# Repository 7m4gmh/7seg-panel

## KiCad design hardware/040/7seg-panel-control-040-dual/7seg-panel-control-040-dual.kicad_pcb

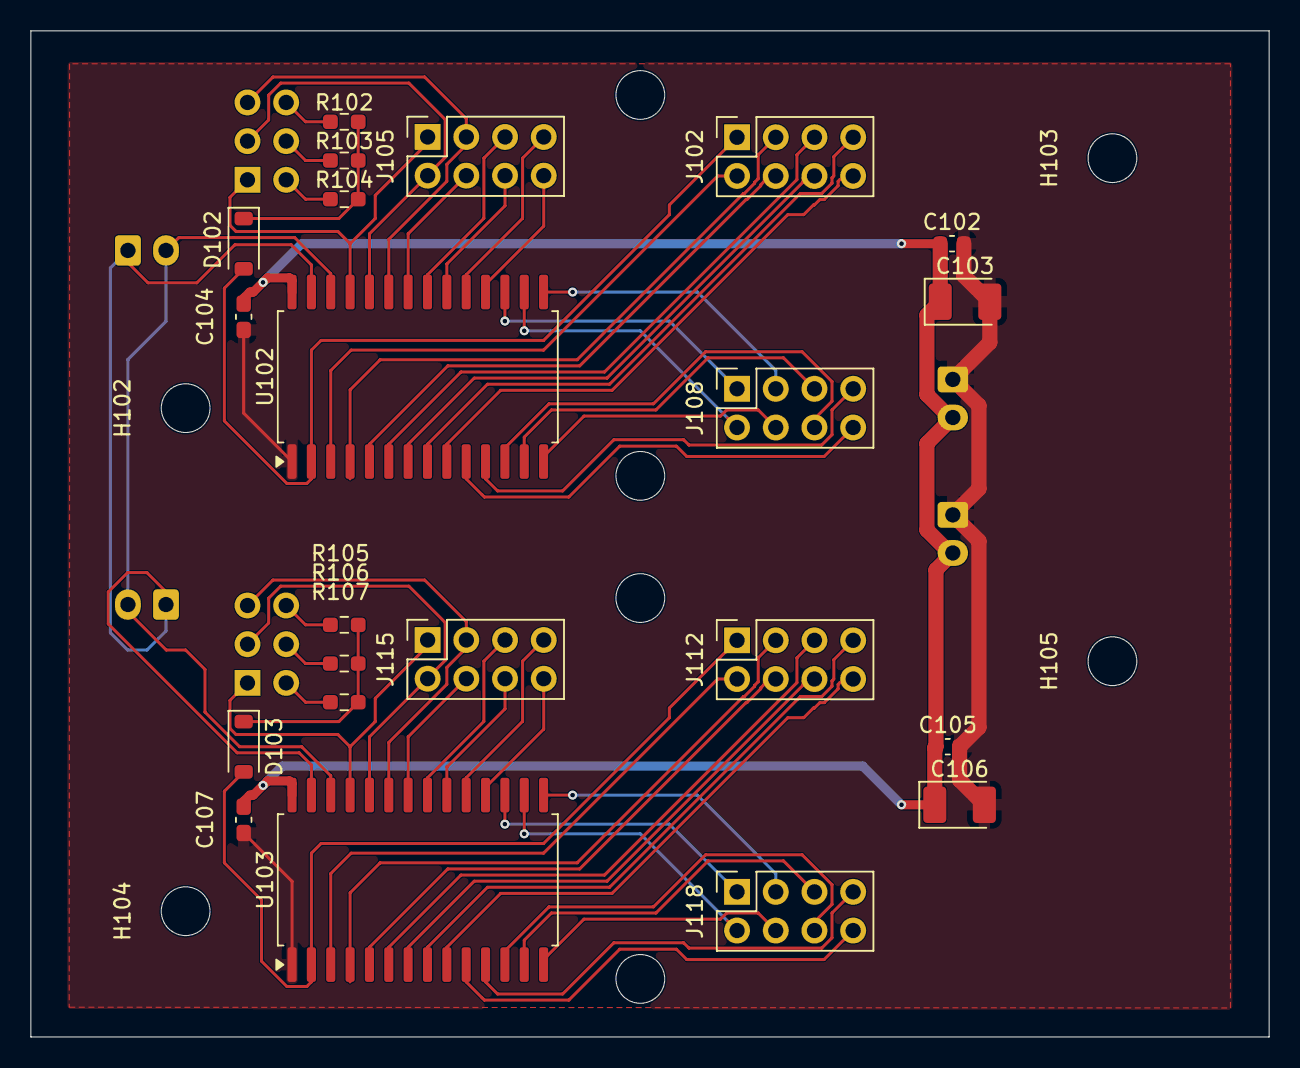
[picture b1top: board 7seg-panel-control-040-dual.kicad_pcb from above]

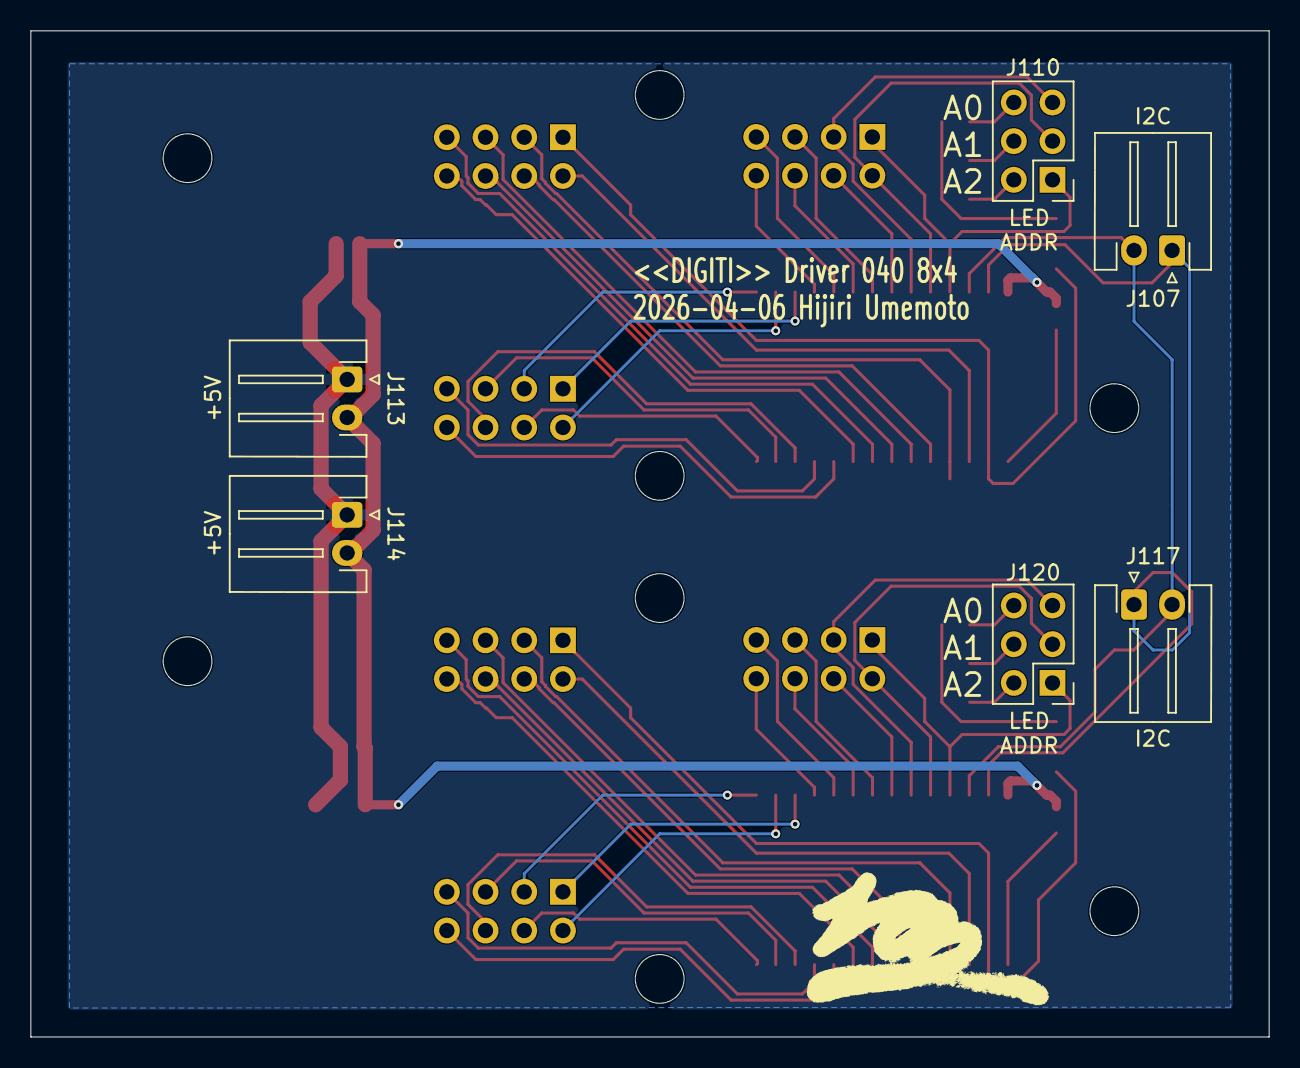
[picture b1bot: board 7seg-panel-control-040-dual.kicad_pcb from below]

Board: 2 copper layers, 81.3 x 66.0 mm, 36 parts (6 on the bottom side), 60 nets.

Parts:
C102, C105: 22uF; C_0603_1608Metric
C103, C106: 22uF; CP_EIA-3528-21_Kemet-B_HandSolder
C104, C107: 0.1uF; C_0603_1608Metric_Pad1.08x0.95mm_HandSolder
D102, D103: 1N4148W; D_SOD-123
H102, H103, H104, H105, H106, H107, H108, H109: MountingHole; MountingHole_3.2mm_M3
J102, J105, J108, J112, J115, J118: Conn_02x04_Odd_Even; PinSocket_2x04_P2.54mm_Vertical
J107, J117: I2C; Generic_XH_S2B-XH-A-1_1x02_P2.50mm_Horizontal
J110, J120: Conn_02x03_Odd_Even; PinHeader_2x03_P2.54mm_Vertical
J113, J114: +5V; Generic_XH_S2B-XH-A-1_1x02_P2.50mm_Horizontal
R102, R103, R104, R105, R106, R107: 39kR; R_0603_1608Metric_Pad0.98x0.95mm_HandSolder
U102, U103: HT16K33-28-SOPA; SOP-28_8.4x18.16mm_P1.27mm

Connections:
A_COM0: D102.2 (A), J102.1, U102.2 (COM0/AD)
A_COM1: J102.2, U102.3 (COM1/KS0)
A_COM2: J102.3, U102.4 (COM2/KS1)
A_COM3: J102.4, U102.5 (COM3/KS2)
A_COM4: J102.5, U102.6 (COM4)
A_COM5: J102.6, U102.7 (COM5)
A_COM6: J102.7, U102.8 (COM6)
A_COM7: J102.8, U102.9 (COM7)
A_ROW0: J105.1, J110.1, U102.25 (ROW0/A2)
A_ROW1: J105.2, J110.3, U102.24 (ROW1/A1)
A_ROW2: J105.3, J110.5, U102.23 (ROW2/A0)
A_ROW3: J105.4, U102.22 (ROW3/K1)
A_ROW4: J105.5, U102.21 (ROW4/K2)
A_ROW5: J105.6, U102.20 (ROW5/K3)
A_ROW6: J105.7, U102.19 (ROW6/K4)
A_ROW7: J105.8, U102.18 (ROW7/K5)
A_ROW8: J108.1, U102.17 (ROW8/K6)
A_ROW9: J108.2, U102.16 (ROW9/K7)
A_ROW10: J108.3, U102.15 (ROW10/K8)
A_ROW11: J108.4, U102.14 (ROW11/K9)
A_ROW12: J108.5, U102.13 (ROW12/K10)
A_ROW13: J108.6, U102.12 (ROW13/K12)
A_ROW14: J108.7, U102.11 (ROW14/K12)
A_ROW15: J108.8, U102.10 (ROW15/K13/INT)
COM0: D103.2 (A), J112.1, U103.2 (COM0/AD)
COM1: J112.2, U103.3 (COM1/KS0)
COM2: J112.3, U103.4 (COM2/KS1)
COM3: J112.4, U103.5 (COM3/KS2)
COM4: J112.5, U103.6 (COM4)
COM5: J112.6, U103.7 (COM5)
COM6: J112.7, U103.8 (COM6)
COM7: J112.8, U103.9 (COM7)
GND: C102.2, C103.2, C104.2, C105.2, C106.2, C107.2, J113.1, J114.1, U102.1 (VSS), U103.1 (VSS)
unnamed: D102.1 (K), R102.1, R103.1, R104.1
unnamed: D103.1 (K), R105.1, R106.1, R107.1
unnamed: J110.2, R104.2
unnamed: J110.4, R103.2
unnamed: J110.6, R102.2
unnamed: J120.2, R107.2
unnamed: J120.4, R106.2
unnamed: J120.6, R105.2
ROW0: J115.1, J120.1, U103.25 (ROW0/A2)
ROW1: J115.2, J120.3, U103.24 (ROW1/A1)
ROW2: J115.3, J120.5, U103.23 (ROW2/A0)
ROW3: J115.4, U103.22 (ROW3/K1)
ROW4: J115.5, U103.21 (ROW4/K2)
ROW5: J115.6, U103.20 (ROW5/K3)
ROW6: J115.7, U103.19 (ROW6/K4)
ROW7: J115.8, U103.18 (ROW7/K5)
ROW8: J118.1, U103.17 (ROW8/K6)
ROW9: J118.2, U103.16 (ROW9/K7)
ROW10: J118.3, U103.15 (ROW10/K8)
ROW11: J118.4, U103.14 (ROW11/K9)
ROW12: J118.5, U103.13 (ROW12/K10)
ROW13: J118.6, U103.12 (ROW13/K12)
ROW14: J118.7, U103.11 (ROW14/K12)
ROW15: J118.8, U103.10 (ROW15/K13/INT)
SCL: J107.2, J117.2, U102.26 (SCL), U103.26 (SCL)
SDA: J107.1, J117.1, U102.27 (SDA), U103.27 (SDA)
VDD: C102.1, C103.1, C104.1, C105.1, C106.1, C107.1, J113.2, J114.2, U102.28 (VDD), U103.28 (VDD)

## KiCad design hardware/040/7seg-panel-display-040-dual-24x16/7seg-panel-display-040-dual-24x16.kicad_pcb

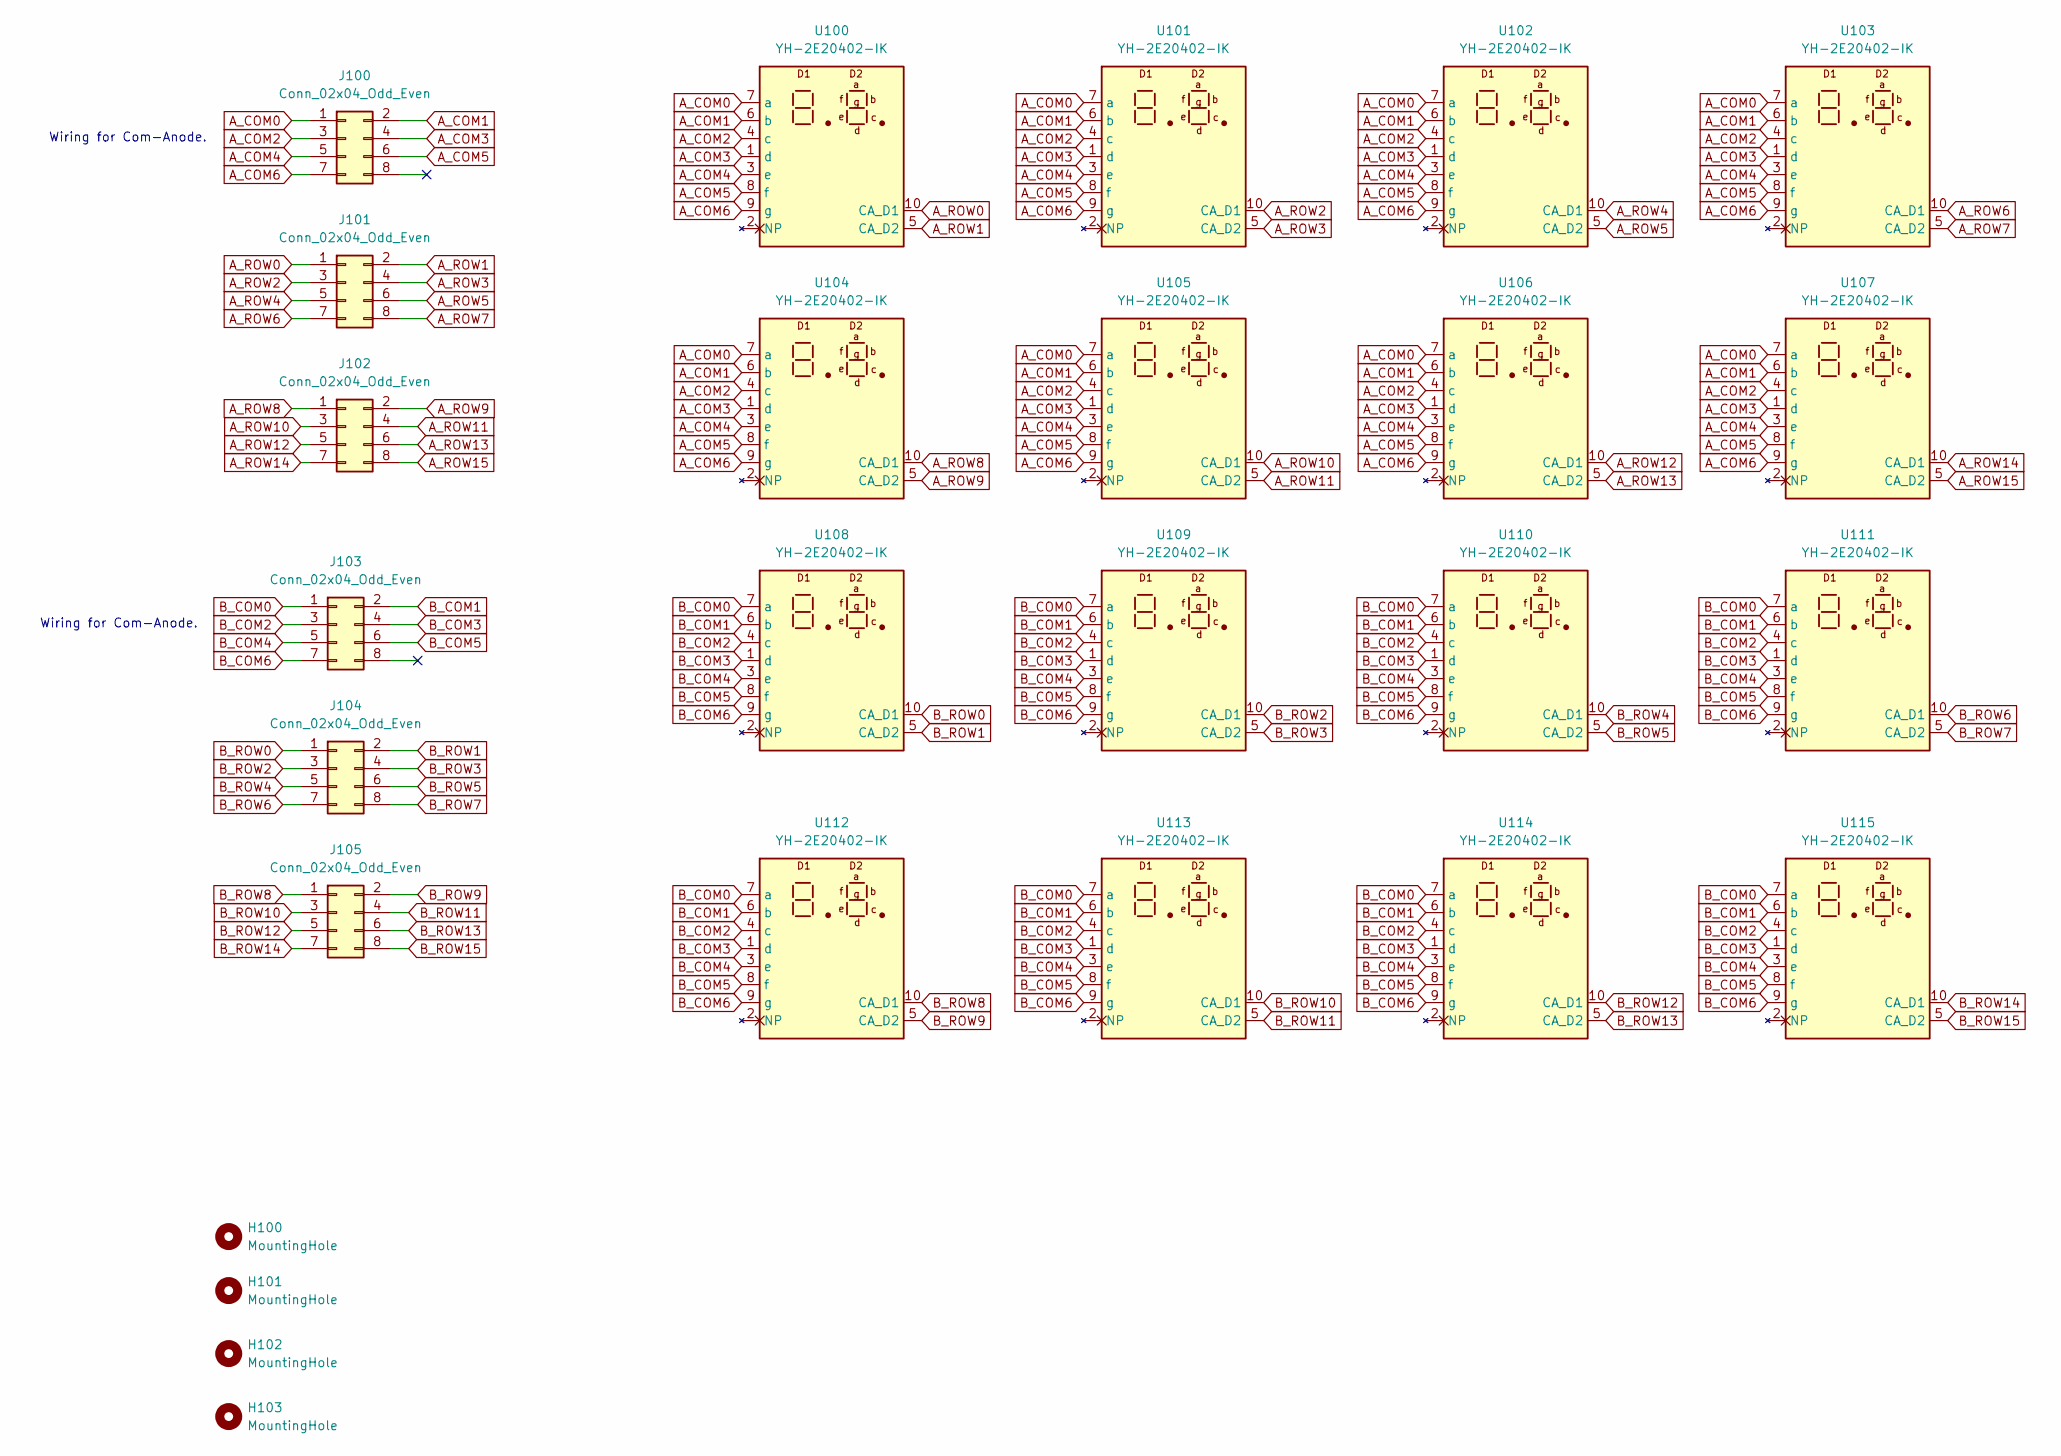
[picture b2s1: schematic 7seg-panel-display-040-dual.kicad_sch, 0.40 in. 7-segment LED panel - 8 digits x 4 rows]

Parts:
H100, H101, H102, H103: MountingHole; MountingHole_3.2mm_M3
J100, J101, J102, J103, J104, J105: Conn_02x04_Odd_Even; PinHeader_2x04_P2.54mm_Vertical
U100, U101, U102, U103, U104, U105, U106, U107, U108, U109, U110, U111, U112, U113, U114, U115: YH-2E20402-IK; YH-2E20402-12P

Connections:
A_COM0: J100.1, U100.7 (a), U101.7 (a), U102.7 (a), U103.7 (a), U104.7 (a), U105.7 (a), U106.7 (a), U107.7 (a)
A_COM1: J100.2, U100.6 (b), U101.6 (b), U102.6 (b), U103.6 (b), U104.6 (b), U105.6 (b), U106.6 (b), U107.6 (b)
A_COM2: J100.3, U100.4 (c), U101.4 (c), U102.4 (c), U103.4 (c), U104.4 (c), U105.4 (c), U106.4 (c), U107.4 (c)
A_COM3: J100.4, U100.1 (d), U101.1 (d), U102.1 (d), U103.1 (d), U104.1 (d), U105.1 (d), U106.1 (d), U107.1 (d)
A_COM4: J100.5, U100.3 (e), U101.3 (e), U102.3 (e), U103.3 (e), U104.3 (e), U105.3 (e), U106.3 (e), U107.3 (e)
A_COM5: J100.6, U100.8 (f), U101.8 (f), U102.8 (f), U103.8 (f), U104.8 (f), U105.8 (f), U106.8 (f), U107.8 (f)
A_COM6: J100.7, U100.9 (g), U101.9 (g), U102.9 (g), U103.9 (g), U104.9 (g), U105.9 (g), U106.9 (g), U107.9 (g)
A_ROW0: J101.1, U100.10 (CA_D1)
A_ROW1: J101.2, U100.5 (CA_D2)
A_ROW2: J101.3, U101.10 (CA_D1)
A_ROW3: J101.4, U101.5 (CA_D2)
A_ROW4: J101.5, U102.10 (CA_D1)
A_ROW5: J101.6, U102.5 (CA_D2)
A_ROW6: J101.7, U103.10 (CA_D1)
A_ROW7: J101.8, U103.5 (CA_D2)
A_ROW8: J102.1, U104.10 (CA_D1)
A_ROW9: J102.2, U104.5 (CA_D2)
A_ROW10: J102.3, U105.10 (CA_D1)
A_ROW11: J102.4, U105.5 (CA_D2)
A_ROW12: J102.5, U106.10 (CA_D1)
A_ROW13: J102.6, U106.5 (CA_D2)
A_ROW14: J102.7, U107.10 (CA_D1)
A_ROW15: J102.8, U107.5 (CA_D2)
B_COM0: J103.1, U108.7 (a), U109.7 (a), U110.7 (a), U111.7 (a), U112.7 (a), U113.7 (a), U114.7 (a), U115.7 (a)
B_COM1: J103.2, U108.6 (b), U109.6 (b), U110.6 (b), U111.6 (b), U112.6 (b), U113.6 (b), U114.6 (b), U115.6 (b)
B_COM2: J103.3, U108.4 (c), U109.4 (c), U110.4 (c), U111.4 (c), U112.4 (c), U113.4 (c), U114.4 (c), U115.4 (c)
B_COM3: J103.4, U108.1 (d), U109.1 (d), U110.1 (d), U111.1 (d), U112.1 (d), U113.1 (d), U114.1 (d), U115.1 (d)
B_COM4: J103.5, U108.3 (e), U109.3 (e), U110.3 (e), U111.3 (e), U112.3 (e), U113.3 (e), U114.3 (e), U115.3 (e)
B_COM5: J103.6, U108.8 (f), U109.8 (f), U110.8 (f), U111.8 (f), U112.8 (f), U113.8 (f), U114.8 (f), U115.8 (f)
B_COM6: J103.7, U108.9 (g), U109.9 (g), U110.9 (g), U111.9 (g), U112.9 (g), U113.9 (g), U114.9 (g), U115.9 (g)
B_ROW0: J104.1, U108.10 (CA_D1)
B_ROW1: J104.2, U108.5 (CA_D2)
B_ROW2: J104.3, U109.10 (CA_D1)
B_ROW3: J104.4, U109.5 (CA_D2)
B_ROW4: J104.5, U110.10 (CA_D1)
B_ROW5: J104.6, U110.5 (CA_D2)
B_ROW6: J104.7, U111.10 (CA_D1)
B_ROW7: J104.8, U111.5 (CA_D2)
B_ROW8: J105.1, U112.10 (CA_D1)
B_ROW9: J105.2, U112.5 (CA_D2)
B_ROW10: J105.3, U113.10 (CA_D1)
B_ROW11: J105.4, U113.5 (CA_D2)
B_ROW12: J105.5, U114.10 (CA_D1)
B_ROW13: J105.6, U114.5 (CA_D2)
B_ROW14: J105.7, U115.10 (CA_D1)
B_ROW15: J105.8, U115.5 (CA_D2)

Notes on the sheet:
Wiring for Com-Anode.

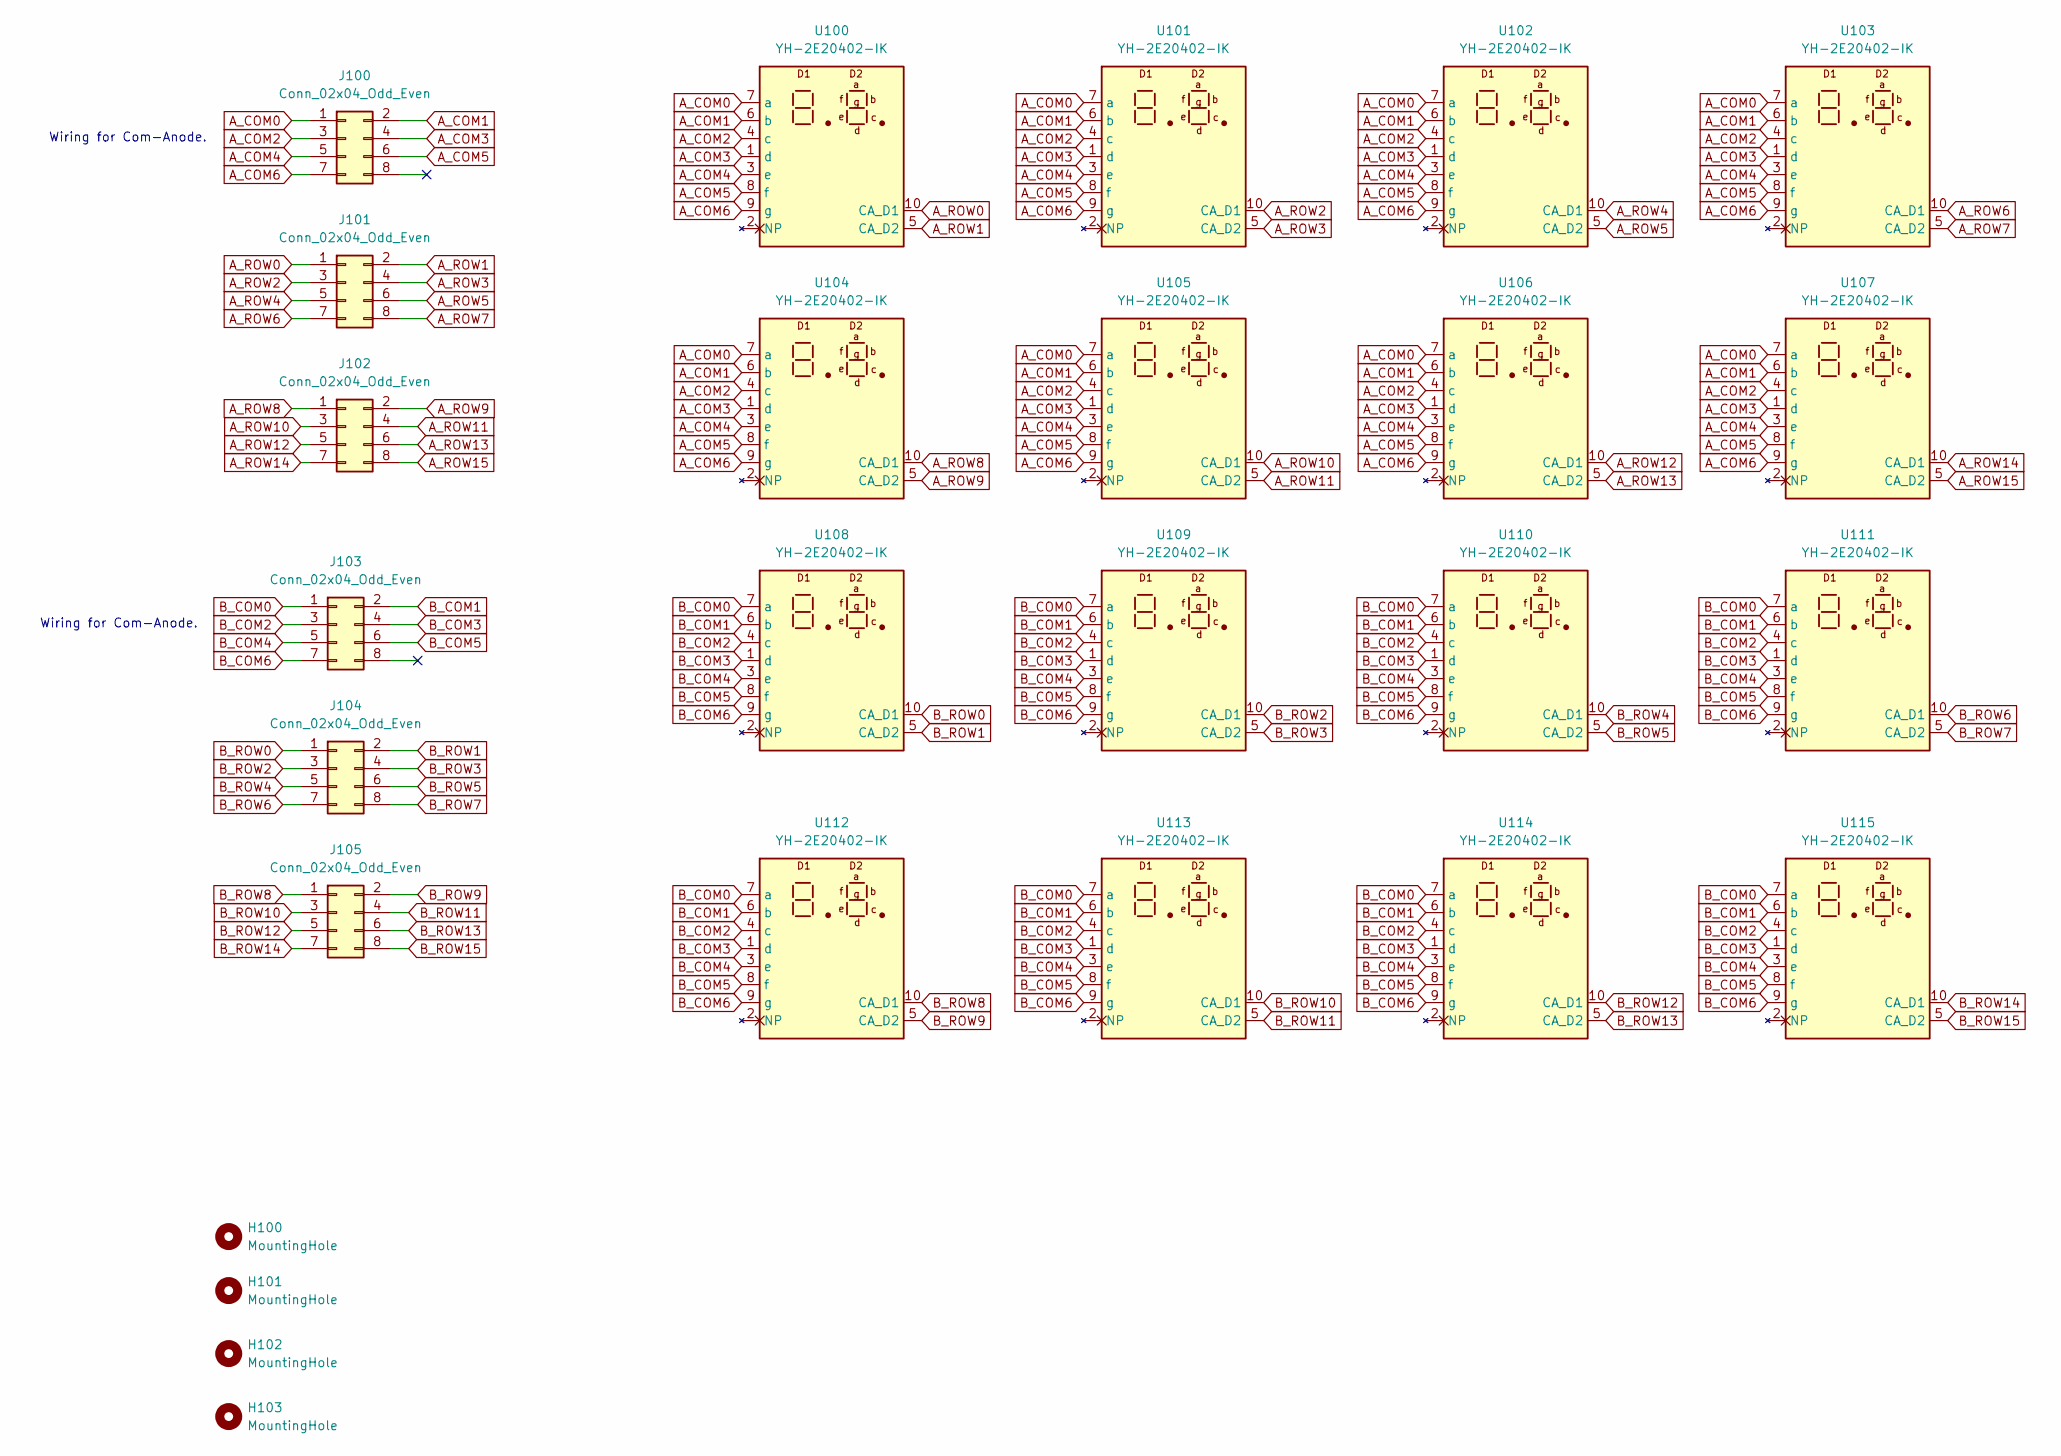
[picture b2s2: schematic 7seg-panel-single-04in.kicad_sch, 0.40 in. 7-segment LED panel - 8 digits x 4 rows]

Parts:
H100, H101, H102, H103: MountingHole; MountingHole_3.2mm_M3
J100, J101, J102, J103, J104, J105: Conn_02x04_Odd_Even; PinHeader_2x04_P2.54mm_Vertical
U100, U101, U102, U103, U104, U105, U106, U107, U108, U109, U110, U111, U112, U113, U114, U115: YH-2E20402-IK; YH-2E20402

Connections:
A_COM0: J100.1, U100.7 (a), U101.7 (a), U102.7 (a), U103.7 (a), U104.7 (a), U105.7 (a), U106.7 (a), U107.7 (a)
A_COM1: J100.2, U100.6 (b), U101.6 (b), U102.6 (b), U103.6 (b), U104.6 (b), U105.6 (b), U106.6 (b), U107.6 (b)
A_COM2: J100.3, U100.4 (c), U101.4 (c), U102.4 (c), U103.4 (c), U104.4 (c), U105.4 (c), U106.4 (c), U107.4 (c)
A_COM3: J100.4, U100.1 (d), U101.1 (d), U102.1 (d), U103.1 (d), U104.1 (d), U105.1 (d), U106.1 (d), U107.1 (d)
A_COM4: J100.5, U100.3 (e), U101.3 (e), U102.3 (e), U103.3 (e), U104.3 (e), U105.3 (e), U106.3 (e), U107.3 (e)
A_COM5: J100.6, U100.8 (f), U101.8 (f), U102.8 (f), U103.8 (f), U104.8 (f), U105.8 (f), U106.8 (f), U107.8 (f)
A_COM6: J100.7, U100.9 (g), U101.9 (g), U102.9 (g), U103.9 (g), U104.9 (g), U105.9 (g), U106.9 (g), U107.9 (g)
A_ROW0: J101.1, U100.10 (CA_D1)
A_ROW1: J101.2, U100.5 (CA_D2)
A_ROW2: J101.3, U101.10 (CA_D1)
A_ROW3: J101.4, U101.5 (CA_D2)
A_ROW4: J101.5, U102.10 (CA_D1)
A_ROW5: J101.6, U102.5 (CA_D2)
A_ROW6: J101.7, U103.10 (CA_D1)
A_ROW7: J101.8, U103.5 (CA_D2)
A_ROW8: J102.1, U104.10 (CA_D1)
A_ROW9: J102.2, U104.5 (CA_D2)
A_ROW10: J102.3, U105.10 (CA_D1)
A_ROW11: J102.4, U105.5 (CA_D2)
A_ROW12: J102.5, U106.10 (CA_D1)
A_ROW13: J102.6, U106.5 (CA_D2)
A_ROW14: J102.7, U107.10 (CA_D1)
A_ROW15: J102.8, U107.5 (CA_D2)
B_COM0: J103.1, U108.7 (a), U109.7 (a), U110.7 (a), U111.7 (a), U112.7 (a), U113.7 (a), U114.7 (a), U115.7 (a)
B_COM1: J103.2, U108.6 (b), U109.6 (b), U110.6 (b), U111.6 (b), U112.6 (b), U113.6 (b), U114.6 (b), U115.6 (b)
B_COM2: J103.3, U108.4 (c), U109.4 (c), U110.4 (c), U111.4 (c), U112.4 (c), U113.4 (c), U114.4 (c), U115.4 (c)
B_COM3: J103.4, U108.1 (d), U109.1 (d), U110.1 (d), U111.1 (d), U112.1 (d), U113.1 (d), U114.1 (d), U115.1 (d)
B_COM4: J103.5, U108.3 (e), U109.3 (e), U110.3 (e), U111.3 (e), U112.3 (e), U113.3 (e), U114.3 (e), U115.3 (e)
B_COM5: J103.6, U108.8 (f), U109.8 (f), U110.8 (f), U111.8 (f), U112.8 (f), U113.8 (f), U114.8 (f), U115.8 (f)
B_COM6: J103.7, U108.9 (g), U109.9 (g), U110.9 (g), U111.9 (g), U112.9 (g), U113.9 (g), U114.9 (g), U115.9 (g)
B_ROW0: J104.1, U108.10 (CA_D1)
B_ROW1: J104.2, U108.5 (CA_D2)
B_ROW2: J104.3, U109.10 (CA_D1)
B_ROW3: J104.4, U109.5 (CA_D2)
B_ROW4: J104.5, U110.10 (CA_D1)
B_ROW5: J104.6, U110.5 (CA_D2)
B_ROW6: J104.7, U111.10 (CA_D1)
B_ROW7: J104.8, U111.5 (CA_D2)
B_ROW8: J105.1, U112.10 (CA_D1)
B_ROW9: J105.2, U112.5 (CA_D2)
B_ROW10: J105.3, U113.10 (CA_D1)
B_ROW11: J105.4, U113.5 (CA_D2)
B_ROW12: J105.5, U114.10 (CA_D1)
B_ROW13: J105.6, U114.5 (CA_D2)
B_ROW14: J105.7, U115.10 (CA_D1)
B_ROW15: J105.8, U115.5 (CA_D2)

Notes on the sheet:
Wiring for Com-Anode.

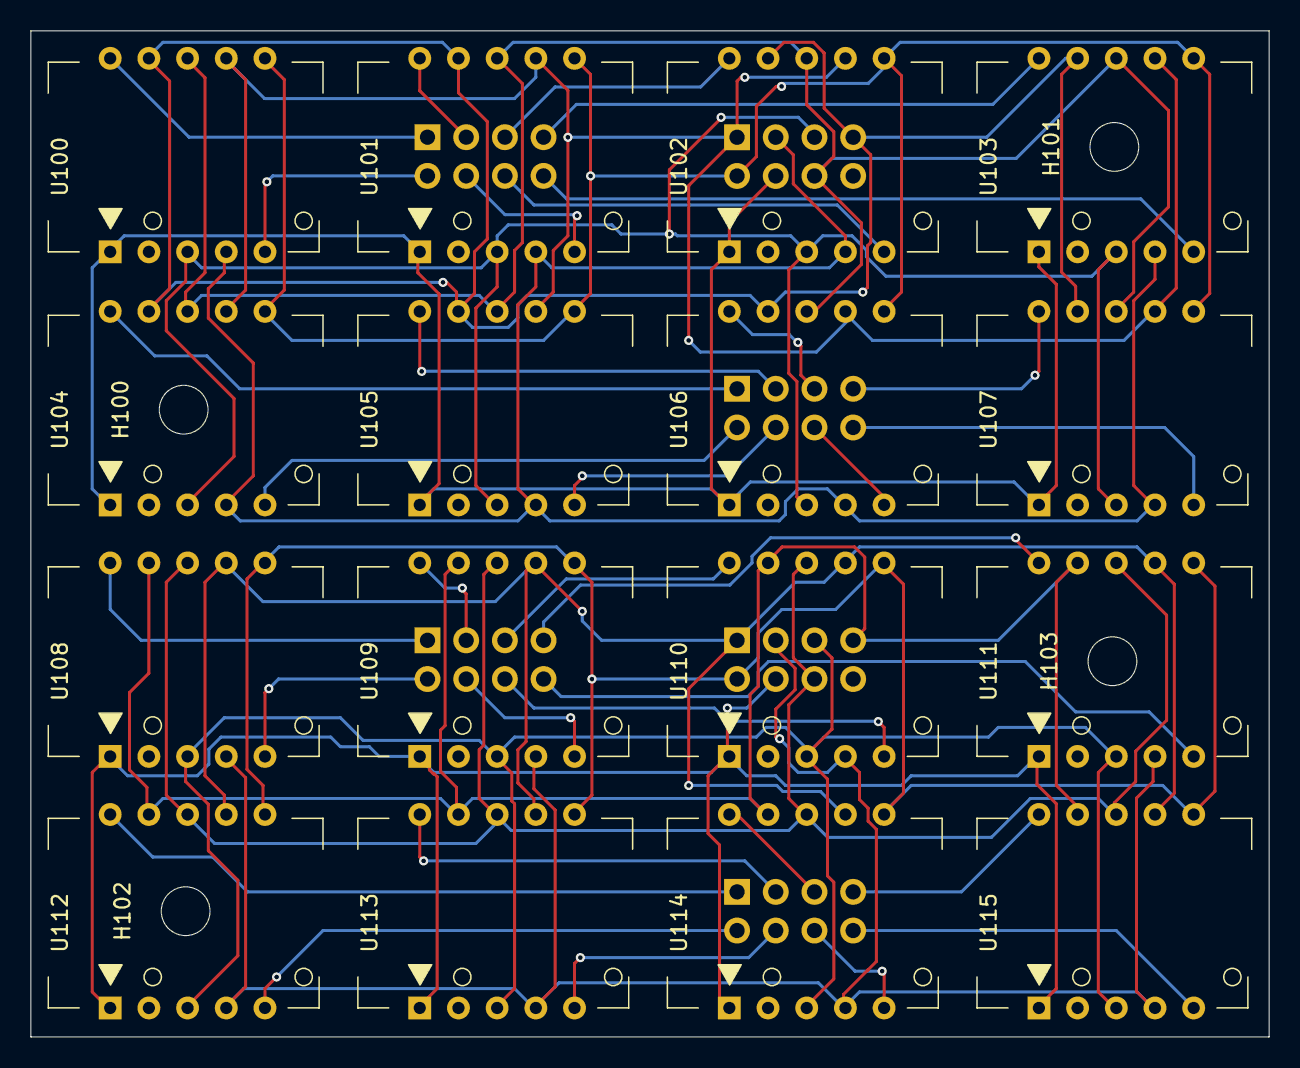
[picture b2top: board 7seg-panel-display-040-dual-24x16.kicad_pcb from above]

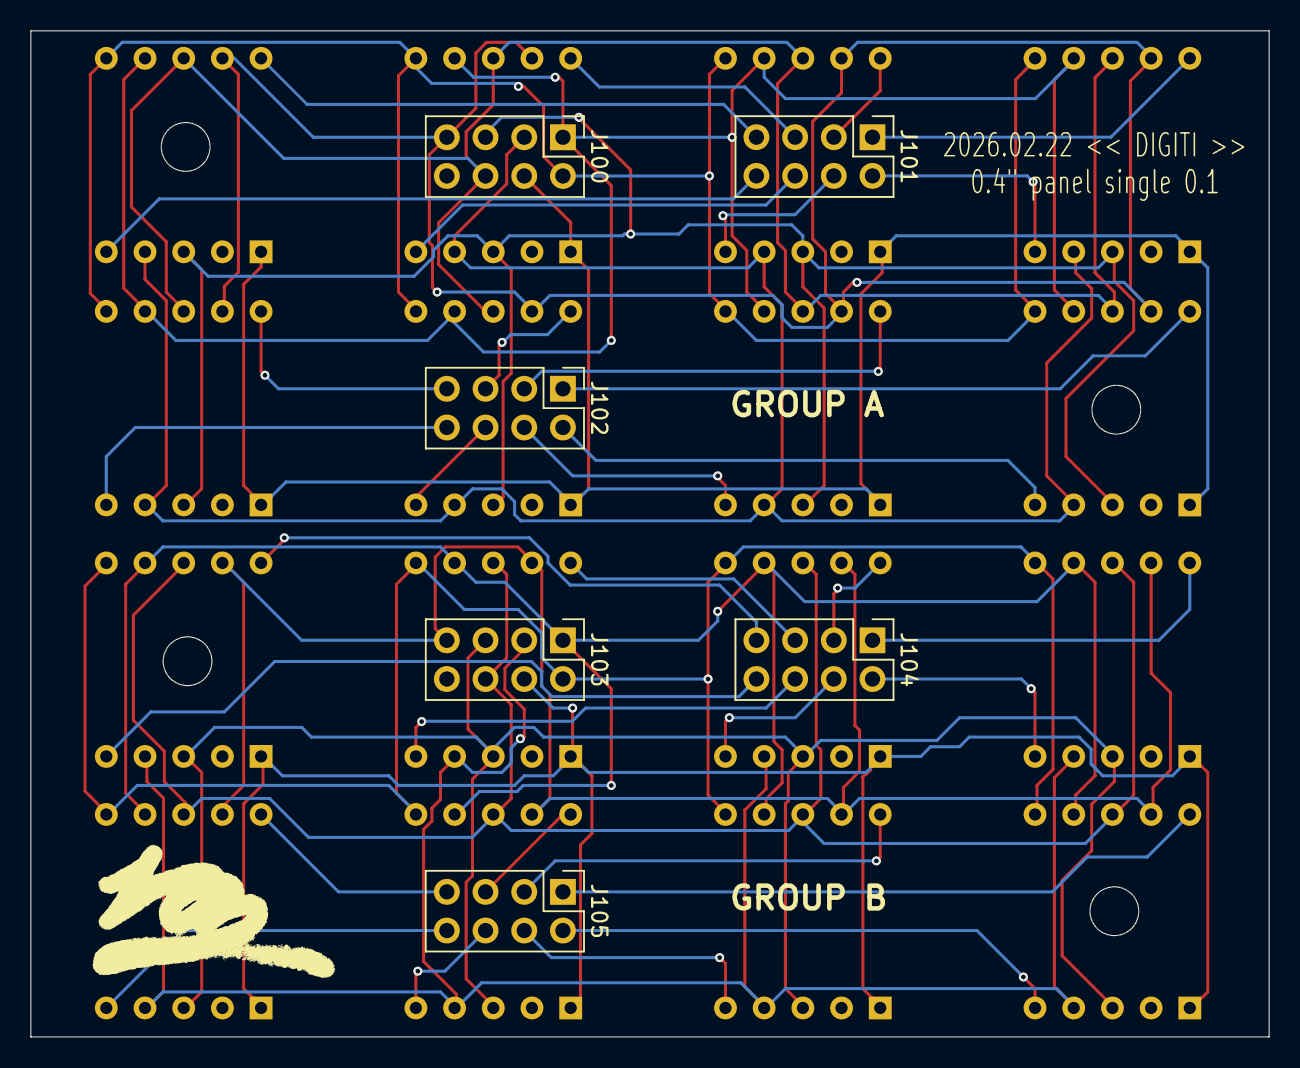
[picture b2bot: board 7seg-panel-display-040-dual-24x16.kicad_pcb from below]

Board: 2 copper layers, 81.3 x 66.0 mm, 26 parts (6 on the bottom side), 46 nets.

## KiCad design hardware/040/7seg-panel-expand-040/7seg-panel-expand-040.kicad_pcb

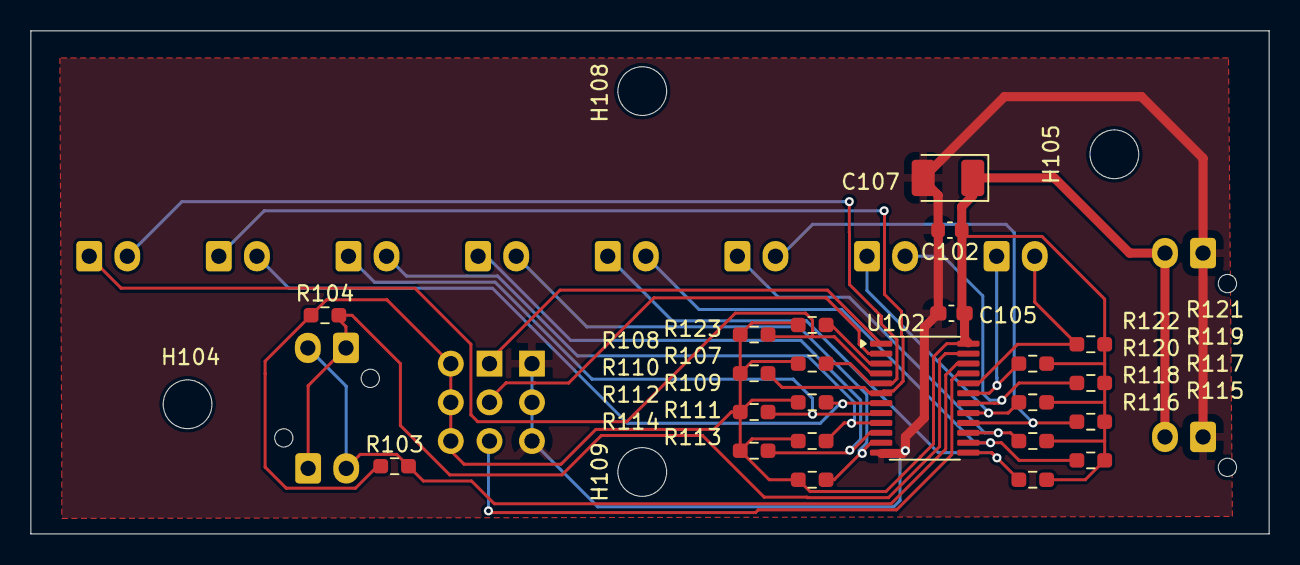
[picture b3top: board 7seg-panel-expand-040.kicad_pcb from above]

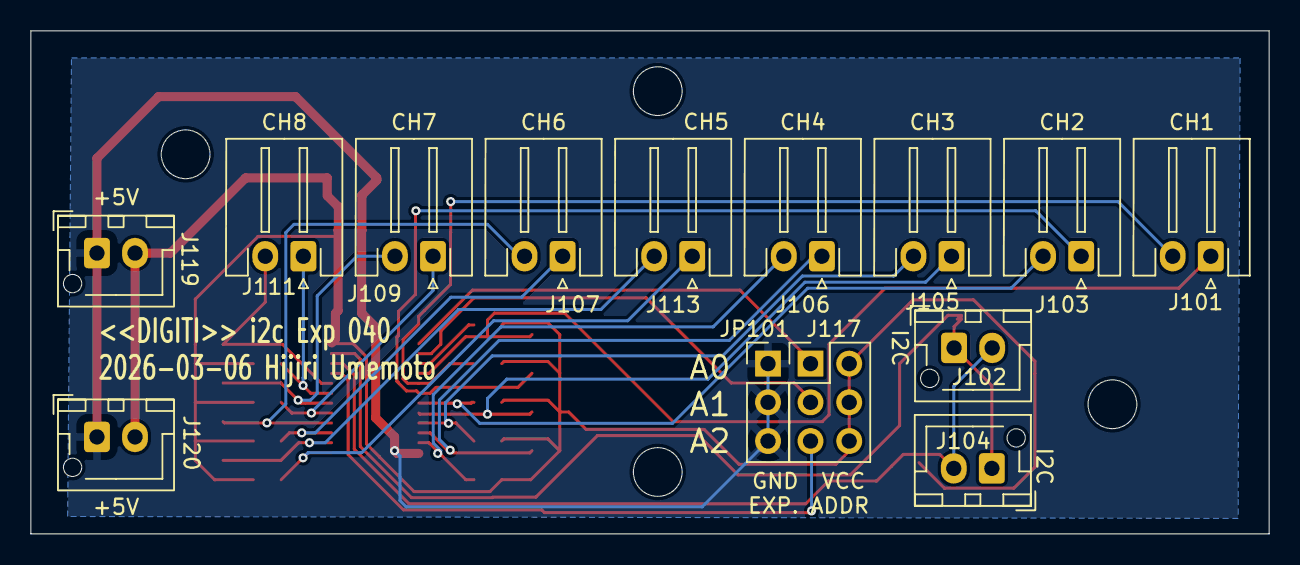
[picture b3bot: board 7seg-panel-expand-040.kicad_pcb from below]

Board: 2 copper layers, 81.3 x 33.0 mm, 41 parts (14 on the bottom side), 24 nets.

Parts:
C102: 22uF; C_0603_1608Metric
C105: 0.1uF; C_0603_1608Metric_Pad1.08x0.95mm_HandSolder
C107: 22uF; CP_EIA-3528-21_Kemet-B_HandSolder
H104, H105, H108, H109: MountingHole; MountingHole_3.2mm_M3
J101: CH1; Generic_XH_S2B-XH-A-1_1x02_P2.50mm_Horizontal
J102, J104: I2C; JST_XH_B2B-XH-AM_1x02_P2.50mm_Vertical
J103: CH2; Generic_XH_S2B-XH-A-1_1x02_P2.50mm_Horizontal
J105: CH3; Generic_XH_S2B-XH-A-1_1x02_P2.50mm_Horizontal
J106: CH4; Generic_XH_S2B-XH-A-1_1x02_P2.50mm_Horizontal
J107: CH6; Generic_XH_S2B-XH-A-1_1x02_P2.50mm_Horizontal
J109: CH7; Generic_XH_S2B-XH-A-1_1x02_P2.50mm_Horizontal
J111: CH8; Generic_XH_S2B-XH-A-1_1x02_P2.50mm_Horizontal
J113: CH5; Generic_XH_S2B-XH-A-1_1x02_P2.50mm_Horizontal
J117: Conn_02x03_Odd_Even; PinHeader_2x03_P2.54mm_Vertical
J119, J120: +5V; JST_XH_B2B-XH-AM_1x02_P2.50mm_Vertical
JP101: A2; PinHeader_1x03_P2.54mm_Vertical
R103, R104, R107, R108, R109, R110, R111, R112, R113, R114, R115, R116, R117, R118, R119, R120, R121, R122, R123: 4.7kR; R_0603_1608Metric_Pad0.98x0.95mm_HandSolder
U102: TCA9548APWR; TSSOP-24_4.4x7.8mm_P0.65mm

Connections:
EX_SCL: J102.2, J104.2, R103.2, U102.22 (SCL)
EX_SDA: J102.1, J104.1, R104.2, U102.23 (SDA)
GND2: C102.2, C105.2, C107.2, J119.1, J120.1, JP101.1, JP101.2, JP101.3, U102.12 (GND)
unnamed: J117.1, U102.1 (A0)
unnamed: J117.3, U102.2 (A1)
unnamed: J117.5, U102.21 (A2)
unnamed: R123.2, U102.3 (~RESET)
SC0: J101.2, R107.2, U102.5 (SC0)
SC1: J103.2, R109.2, U102.7 (SC1)
SC2: J105.2, R111.2, U102.9 (SC2)
SC3: J106.2, R113.2, U102.11 (SC3)
SC4: J113.2, R115.2, U102.14 (SC4)
SC5: J107.2, R117.2, U102.16 (SC5)
SC6: J109.2, R119.2, U102.18 (SC6)
SC7: J111.2, R121.2, U102.20 (SC7)
SD0: J101.1, R108.2, U102.4 (SD0)
SD1: J103.1, R110.2, U102.6 (SD1)
SD2: J105.1, R112.2, U102.8 (SD2)
SD3: J106.1, R114.2, U102.10 (SD3)
SD4: J113.1, R116.2, U102.13 (SD4)
SD5: J107.1, R118.2, U102.15 (SD5)
SD6: J109.1, R120.2, U102.17 (SD6)
SD7: J111.1, R122.2, U102.19 (SD7)
VCC2: C102.1, C105.1, C107.1, J117.2, J117.4, J117.6, J119.2, J120.2, R103.1, R104.1, R107.1, R108.1, R109.1, R110.1, R111.1, R112.1, R113.1, R114.1, R115.1, R116.1, R117.1, R118.1, R119.1, R120.1, R121.1, R122.1, R123.1, U102.24 (VCC)

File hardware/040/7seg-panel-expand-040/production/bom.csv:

Designator,Footprint,Quantity,Value,LCSC Part #
C102,0603,1,22uF,
C105,0603,1,0.1uF,
J101,Generic_XH_S2B-XH-A-1_1x02_P2.50mm_Horizontal,1,CH1,
"J102, J104",JST_XH_B2B-XH-AM_1x02_P2.50mm_Vertical,2,I2C,
J103,Generic_XH_S2B-XH-A-1_1x02_P2.50mm_Horizontal,1,CH2,
J105,Generic_XH_S2B-XH-A-1_1x02_P2.50mm_Horizontal,1,CH3,
J106,Generic_XH_S2B-XH-A-1_1x02_P2.50mm_Horizontal,1,CH4,
J107,Generic_XH_S2B-XH-A-1_1x02_P2.50mm_Horizontal,1,CH6,
J109,Generic_XH_S2B-XH-A-1_1x02_P2.50mm_Horizontal,1,CH7,
J111,Generic_XH_S2B-XH-A-1_1x02_P2.50mm_Horizontal,1,CH8,
J113,Generic_XH_S2B-XH-A-1_1x02_P2.50mm_Horizontal,1,CH5,
J117,PinHeader_2x03_P2.54mm_Vertical,1,Conn_02x03_Odd_Even,
"J119, J120",JST_XH_B2B-XH-AM_1x02_P2.50mm_Vertical,2,+5V,
JP101,PinHeader_1x03_P2.54mm_Vertical,1,A2,
"R107, R108, R109, R110, R111, R112, R113, R114, R115, R116, R117, R118, R119, R120, R121, R122, R123",0603,17,4.7kR,
U102,TSSOP-24_4.4x7.8mm_P0.65mm,1,TCA9548APWR,
